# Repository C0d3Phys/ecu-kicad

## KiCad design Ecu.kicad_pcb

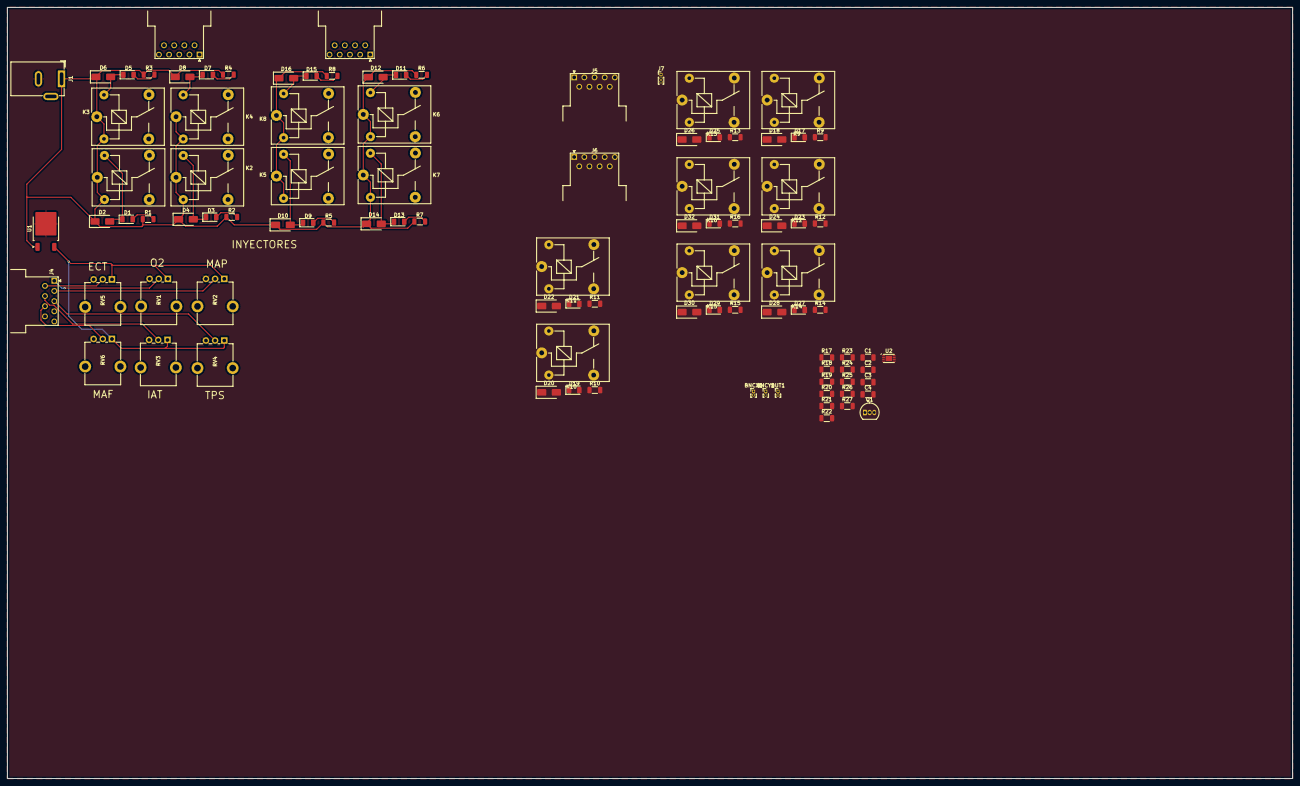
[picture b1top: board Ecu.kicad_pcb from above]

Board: 2 copper layers, 350.0 x 210.0 mm, 98 parts (0 on the bottom side), 57 nets.

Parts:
BNCX1: Conn_01x02_Pin; PinHeader_1x02_P1.00mm_Vertical
BNCY1: Conn_01x02_Pin; PinHeader_1x02_P1.00mm_Vertical
C1, C2, C3, C4: C; C_1206_3216Metric
D1, D3, D5, D7, D9, D11, D13, D15, D17, D19, D21, D23, D25, D27, D29, D31: LED; LED_1206_3216Metric
D2, D4, D6, D8, D10, D12, D14, D16, D18, D20, D22, D24, D26, D28, D30, D32: D_Schottky; D_SMA
DUT1: Conn_01x02_Pin; PinHeader_1x02_P1.00mm_Vertical
J1: Barrel_Jack_MountingPin; BarrelJack_GCT_DCJ200-10-A_Horizontal
J2, J3, J4, J5, J6: DE9_Pins; DSUB-9_Pins_Horizontal_P2.77x2.54mm_EdgePinOffset9.40mm
J7: Conn_01x03_Pin; PinHeader_1x03_P1.00mm_Vertical
K1, K2, K3, K4, K5, K6, K7, K8, K9, K10, K11, K12, K13, K14, K15, K16: SANYOU_SRD_Form_C; Relay_SPDT_SANYOU_SRD_Series_Form_C
Q1: 2N3904; TO-92_Inline
R1, R2, R3, R4, R5, R6, R7, R8, R9, R10, R11, R12, R13, R14, R15, R16, R17, R18, R19, R20, R21, R22, R23, R24, R25, R26, R27: R; R_1206_3216Metric
RV1, RV2, RV3, RV4, RV5, RV6: R_Potentiometer; Potentiometer_Alpha_RD901F-40-00D_Single_Vertical_CircularH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
U1: L7805; TO-252-2
U2: MCP6002-xMC; DFN-8-1EP_3x2mm_P0.5mm_EP1.75x1.45mm

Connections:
+12V: D2.1 (K), D4.1 (K), D6.1 (K), D8.1 (K), D10.1 (K), D12.1 (K), D14.1 (K), D16.1 (K), J1.1, J7.3, K1.1, K1.2, K2.1, K2.2, K3.1, K3.2, K4.1, K4.2, K5.1, K5.2, K6.1, K6.2, K7.1, K7.2, K8.1, K8.2, R1.1, R2.1, R3.1, R4.1, R5.1, R6.1, R7.1, R8.1, U1.1 (IN)
/<NO NET>: J3.6, J5.6
/CINY8/VDD: D18.1 (K), K9.1, K9.2, R9.1
/CINY10/VDD: D22.1 (K), K11.1, K11.2, R11.1
/SECT: J4.6, RV5.2
/SIAT: J4.7, RV3.2
/SMAF: J4.8, RV6.2
/SMAP: J4.2, RV2.2
/SO2: J4.1, RV1.2
/STPS: J4.3, RV4.2
/Trace Curve/AGND: BNCX1.1, BNCY1.1, DUT1.1, R27.2
/Trace Curve/VREF: R20.1, R25.1, U2.8 (V+)
/VD: D20.1 (K), D24.1 (K), D26.1 (K), D28.1 (K), D30.1 (K), D32.1 (K), J7.2, K10.1, K10.2, K12.1, K12.2, K13.1, K13.2, K14.1, K14.2, K15.1, K15.2, K16.1, K16.2, R10.1, R12.1, R13.1, R14.1, R15.1, R16.1
GND: J1.2, J7.1, Q1.1 (E), R17.2, R18.2, R22.2, R26.2, RV1.3, RV2.3, RV3.3, RV4.3, RV5.3, RV6.3, U1.2 (GND), U2.4 (V-), U2.9 (V-)
unnamed: BNCX1.2, DUT1.2, R23.1, U2.1, U2.2 (-)
unnamed: BNCY1.2, R24.2, R27.1, U2.7
unnamed: C1.2, C2.2, R17.1
unnamed: C2.1, C3.2, R18.1
unnamed: C4.2, R21.1
unnamed: D1.2 (A), R1.2
unnamed: D1.1 (K), D2.2 (A), K1.5
unnamed: D3.2 (A), R2.2
unnamed: D3.1 (K), D4.2 (A), K2.5
unnamed: D5.2 (A), R3.2
unnamed: D5.1 (K), D6.2 (A), K3.5
unnamed: D7.2 (A), R4.2
unnamed: D7.1 (K), D8.2 (A), K4.5
unnamed: D9.2 (A), R5.2
unnamed: D9.1 (K), D10.2 (A), K5.5
unnamed: D11.2 (A), R6.2
unnamed: D11.1 (K), D12.2 (A), K6.5
unnamed: D13.2 (A), R7.2
unnamed: D13.1 (K), D14.2 (A), K7.5
unnamed: D15.2 (A), R8.2
unnamed: D15.1 (K), D16.2 (A), K8.5
unnamed: D17.2 (A), R9.2
unnamed: D17.1 (K), D18.2 (A), K9.5
unnamed: D19.2 (A), R10.2
unnamed: D19.1 (K), D20.2 (A), K10.5
unnamed: D21.2 (A), R11.2
unnamed: D21.1 (K), D22.2 (A), K11.5
unnamed: D23.2 (A), R12.2
unnamed: D23.1 (K), D24.2 (A), K12.5
unnamed: D25.2 (A), R13.2
unnamed: D25.1 (K), D26.2 (A), K13.5
unnamed: D27.2 (A), R14.2
unnamed: D27.1 (K), D28.2 (A), K14.5
unnamed: D29.2 (A), R15.2
unnamed: D29.1 (K), D30.2 (A), K15.5
unnamed: D31.2 (A), R16.2
unnamed: D31.1 (K), D32.2 (A), K16.5
unnamed: C3.1, Q1.2 (B), R19.2
unnamed: C1.1, C4.1, Q1.3 (C), R19.1, R20.2
unnamed: R21.2, R22.1, U2.3 (+)
unnamed: R25.2, R26.1, U2.5 (+)
unnamed: R23.2, R24.1, U2.6 (-)
VREF: RV1.1, RV2.1, RV3.1, RV4.1, RV5.1, RV6.1, U1.3 (OUT)

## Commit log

2026-02-17 Init
2026-02-17 vdd for bob
2026-02-17 adding pcb
2026-03-05 trace curve
2026-03-05 new structure
2026-03-05 fix pinout
